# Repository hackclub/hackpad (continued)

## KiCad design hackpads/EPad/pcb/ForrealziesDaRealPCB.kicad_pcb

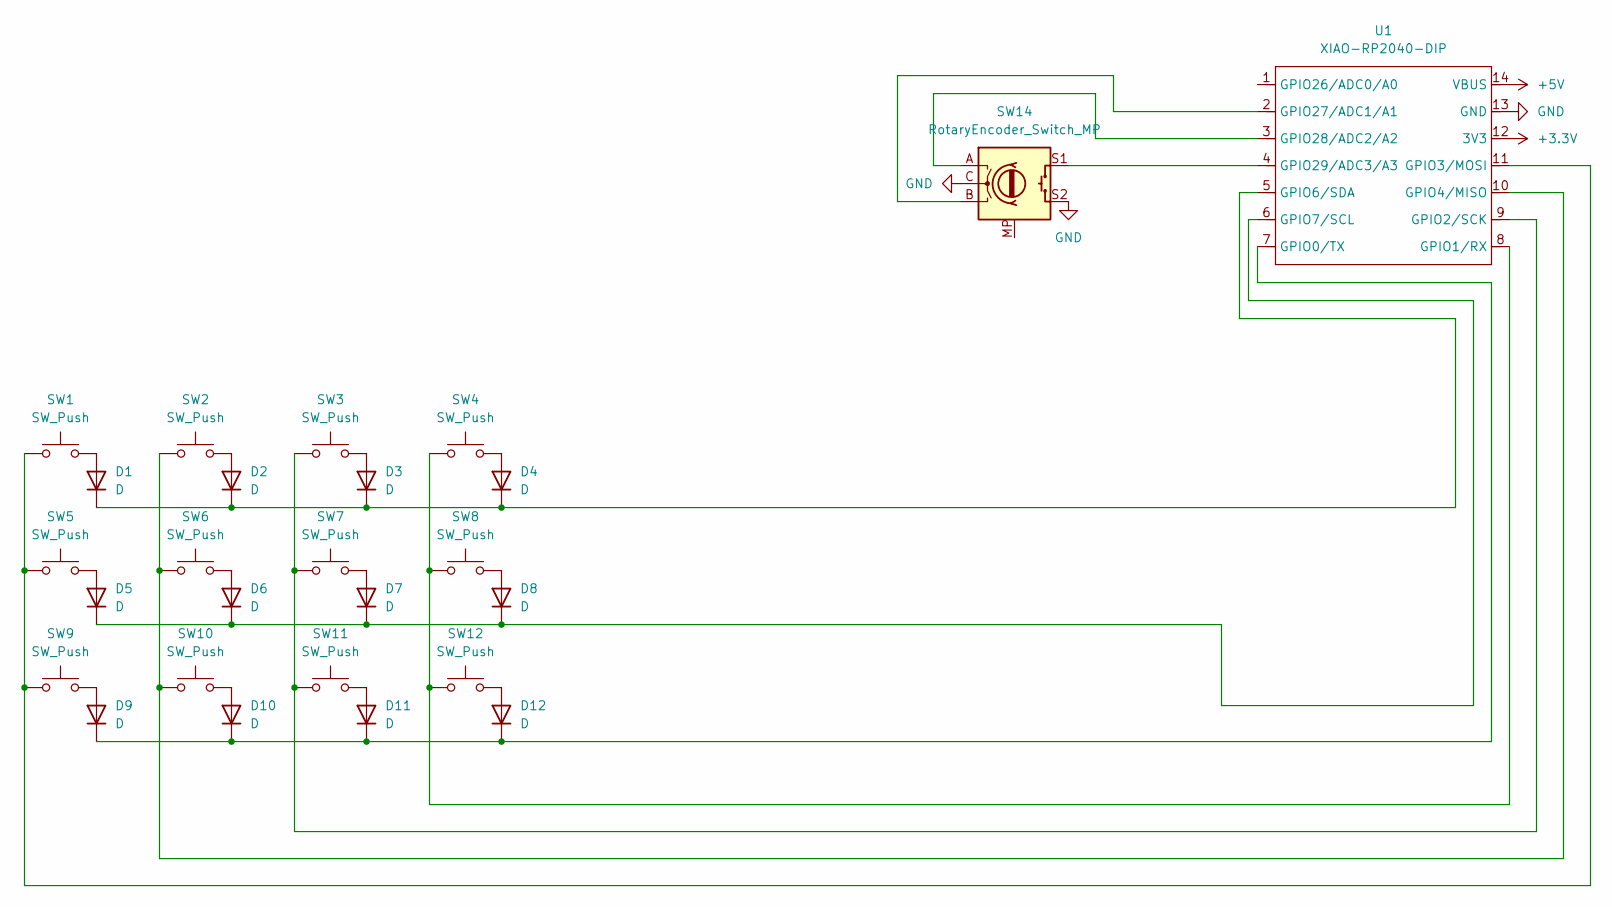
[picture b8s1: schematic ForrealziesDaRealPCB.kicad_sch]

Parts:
D1, D2, D3, D4, D5, D6, D7, D8, D9, D10, D11, D12: D; D_DO-35_SOD27_P7.62mm_Horizontal
SW1, SW2, SW3, SW4, SW5, SW6, SW7, SW8, SW9, SW10, SW11, SW12: SW_Push; SW_Cherry_MX_1.00u_PCB
SW14: RotaryEncoder_Switch_MP; RotaryEncoder_Alps_EC11E-Switch_Vertical_H20mm_CircularMoun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
U1: XIAO-RP2040-DIP

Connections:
+3.3V: U1.12 (3V3)
+5V: U1.14 (VBUS)
GND: SW14.C, SW14.S2, U1.13 (GND)
unnamed: D1.2 (A), SW1.2
unnamed: D1.1 (K), D2.1 (K), D3.1 (K), D4.1 (K), U1.5 (GPIO6/SDA)
unnamed: D2.2 (A), SW2.2
unnamed: D3.2 (A), SW3.2
unnamed: D4.2 (A), SW4.2
unnamed: D5.2 (A), SW5.2
unnamed: D5.1 (K), D6.1 (K), D7.1 (K), D8.1 (K), U1.6 (GPIO7/SCL)
unnamed: D6.2 (A), SW6.2
unnamed: D7.2 (A), SW7.2
unnamed: D8.2 (A), SW8.2
unnamed: D9.2 (A), SW9.2
unnamed: D10.2 (A), SW10.2
unnamed: D9.1 (K), D10.1 (K), D11.1 (K), D12.1 (K), U1.7 (GPIO0/TX)
unnamed: D11.2 (A), SW11.2
unnamed: D12.2 (A), SW12.2
unnamed: SW4.1, SW8.1, SW12.1, U1.8 (GPIO1/RX)
unnamed: SW3.1, SW7.1, SW11.1, U1.9 (GPIO2/SCK)
unnamed: SW1.1, SW5.1, SW9.1, U1.11 (GPIO3/MOSI)
unnamed: SW2.1, SW6.1, SW10.1, U1.10 (GPIO4/MISO)
unnamed: SW14.B, U1.2 (GPIO27/ADC1/A1)
unnamed: SW14.A, U1.3 (GPIO28/ADC2/A2)
unnamed: SW14.S1, U1.4 (GPIO29/ADC3/A3)

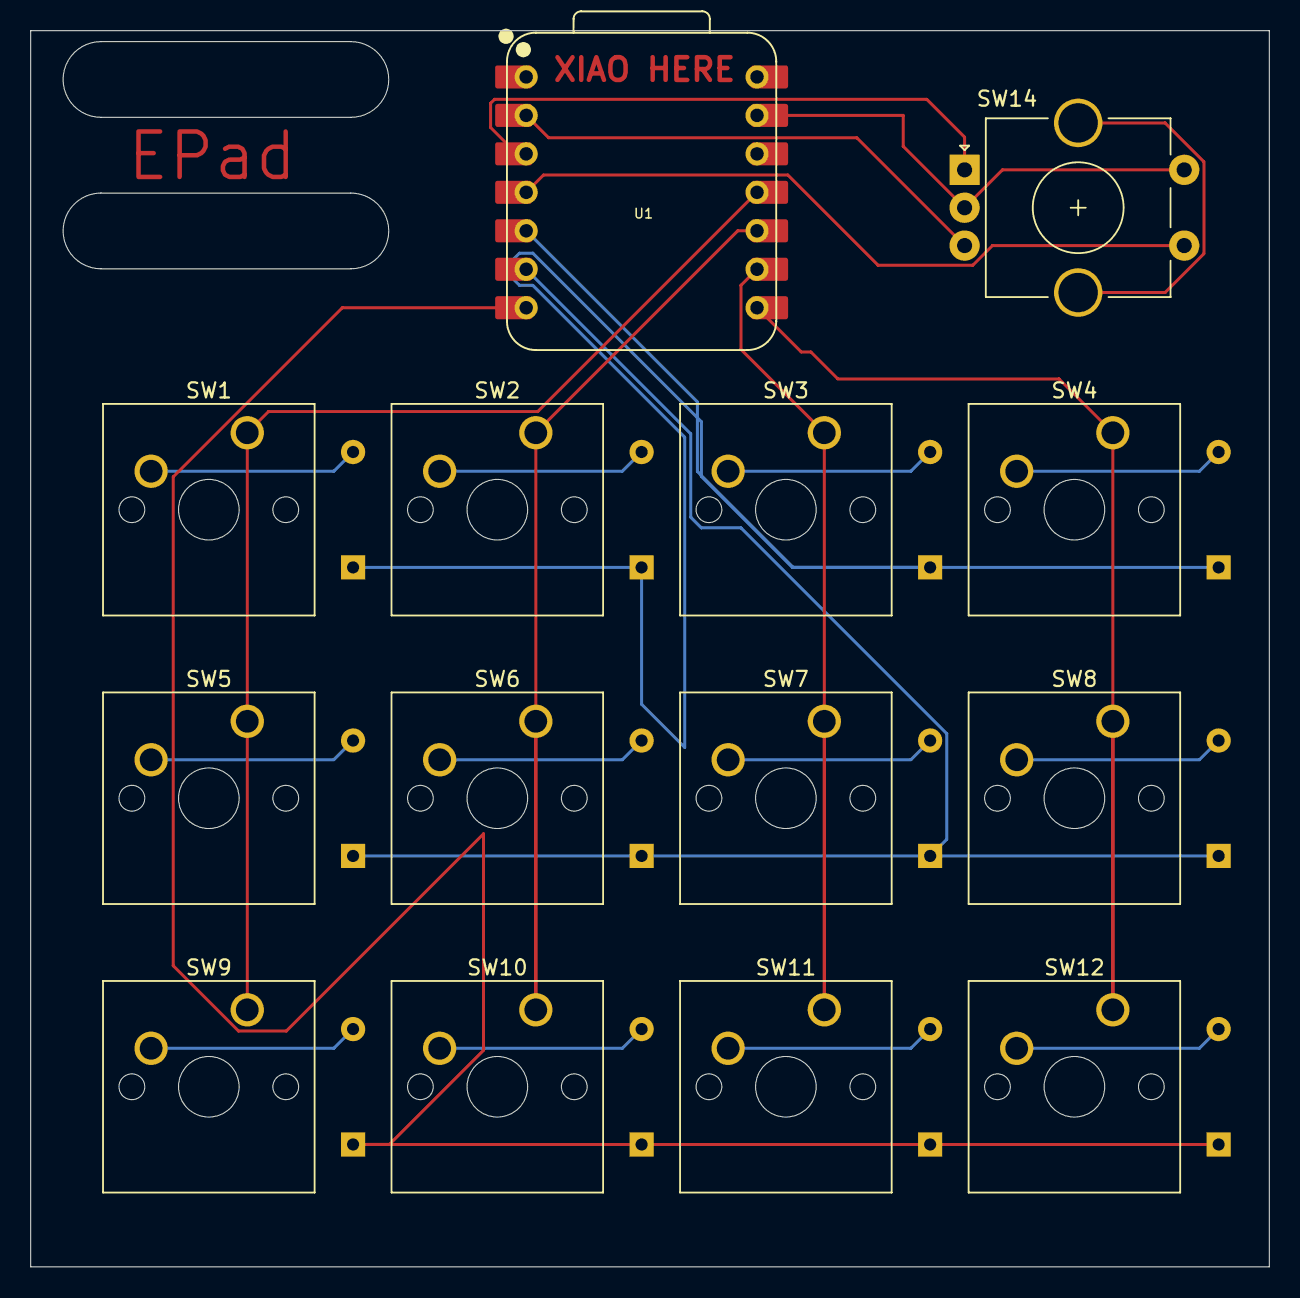
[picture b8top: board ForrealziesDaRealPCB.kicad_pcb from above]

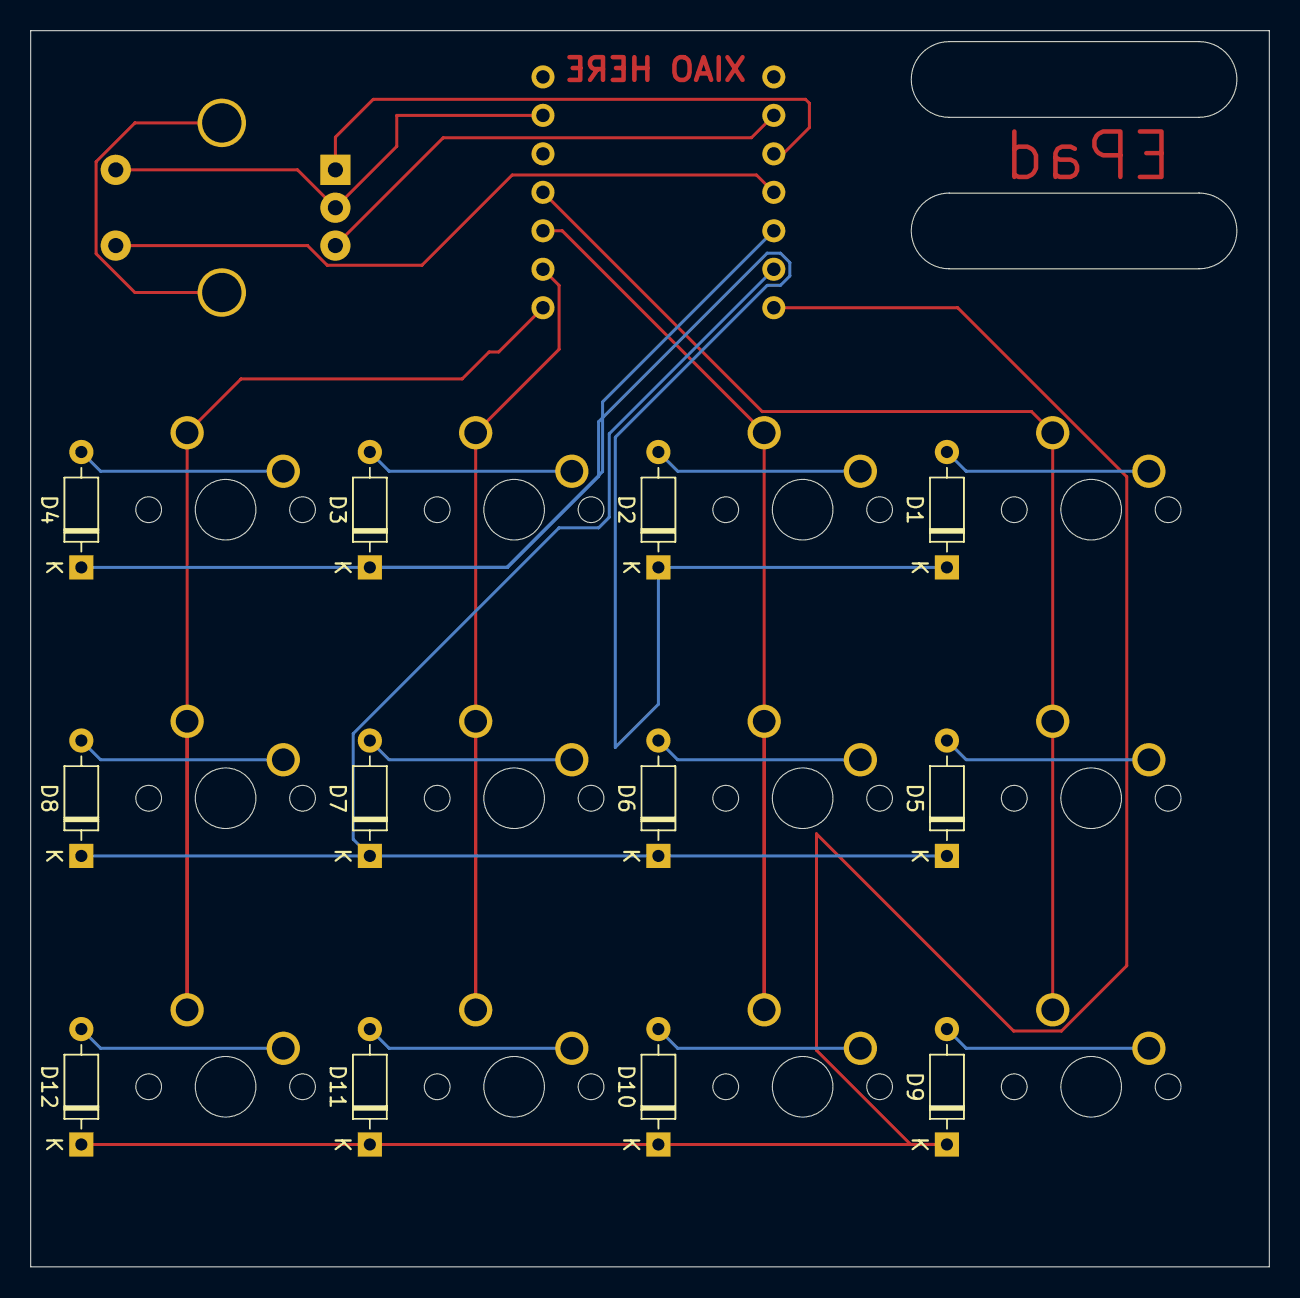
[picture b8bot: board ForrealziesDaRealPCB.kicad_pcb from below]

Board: 2 copper layers, 81.8 x 81.6 mm, 26 parts (12 on the bottom side), 23 nets.
